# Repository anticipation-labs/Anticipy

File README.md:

# Anticipy

Anticipy is a proactive assistant. A phone, a pendant, or a Mac meeting
recorder captures speech; a per-owner server brain interprets it with context
and memory; approved work reaches the owner's own browser, connected apps, or
device "hands"; and every outcome comes back to the phone as a receipt.

**Work on `cloudflare-backend`.** It is the source of record. `main` is an
older, unrelated lineage and is never pushed to; pull requests target
`cloudflare-backend`. Read [HARNESS-LAWS.md](HARNESS-LAWS.md) before changing
anything: meaning belongs to a model with context, never to a regex, word
list, or threshold.

## Components

| Component | Path | What it is |
| --- | --- | --- |
| iPhone app | `app/ios/` | SwiftUI: listening and on-device transcription, pendant BLE (`app/ios/Anticipy/BLE/`), replies, connected apps |
| Mac app | `app/macos/` | Meeting recorder; unsigned build in CI, signed release through `mac-release.yml` |
| Chrome extension | `extension/` | MV3 "hands" in the owner's own logged-in Chrome; packaged into three ZIP aliases under `migration/workers/public/` |
| API Worker | `migration/workers/` | Cloudflare Worker (TypeScript) with D1, R2 and a Durable Object; the production API |
| D1 schema and migrations | `migration/d1/` | `schema.sql` plus dated additive migrations |
| Brain Worker + Python brain | `migration/workers/brain/`, `brain/` | Containers fleet, one container per owner, running the Python brain image |
| Pendant firmware | `firmware/` | Zephyr candidate for the XIAO nRF52840 Sense; host-checked here, not built or flashed |
| Gates and proofs | `overnight/`, `proof/` | Scoreboards and live or loopback proofs with green / red / UNPROVEN semantics |
| Python tests | `tests/` | pytest suite over the brain, the gates and a local D1 |
| Contracts | `migration/spec/CONTRACT.md`, `migration/workers/ARCHITECTURE.md` | Behavioural oracle and the Worker reference |

## Data flow

```text
pendant ─BLE─► iPhone ─┐
Mac recorder ──────────┼─► events (D1) ─► brain (one process per owner) ─► jobs ─► hands ─► receipt ─► iPhone
typed / text reply ────┘                   memory.db held in R2             browser · API · device
```

[docs/ARCHITECTURE.md](docs/ARCHITECTURE.md) explains each hop and the
contracts the runtimes share.

## Run every suite

```sh
PYTHON_DOTENV_DISABLED=1 python -m pytest -q
(cd migration/workers && npm test && npx tsc --noEmit)
npm test --prefix migration/workers/brain && npm run typecheck --prefix migration/workers/brain
node extension/tests/run_all.mjs
sh app/ios/Tests/run_all.sh
sh app/macos/Tests/run_all.sh
sh firmware/source/tests/run_firmware_tests.sh
python3 proof/audit/check_extension_package.py
```

[docs/TESTING.md](docs/TESTING.md) says what each suite proves, what it does
not, how to run them offline, and how the installed-extension proof rig works.

## Read next

- [Independent audit, September 15](research/2026-09-15-independent-app-audit.md):
  freshly reproduced checks, corrections to earlier claims, local build 178
  repairs and remaining live acceptance gaps.
- [September 13 readiness board](docs/EOD-READINESS-2026-09-13.md): the earlier
  release evidence and remaining-work board; read with the audit corrections.
- [CHANGELOG.md](CHANGELOG.md): what each release deployed, and what it did
  not prove.
- [docs/ARCHITECTURE.md](docs/ARCHITECTURE.md): runtimes, shared contracts,
  and the evidence ladder.
- [docs/RELEASE.md](docs/RELEASE.md): the ordered release runbook and
  rollback notes.
- [CONTRIBUTING.md](CONTRIBUTING.md): branch model, path-limited commits, the
  iOS build-number rule, and the review expectation.
- [SECURITY.md](SECURITY.md): how to report a vulnerability and where the
  private-data boundary sits.
- [HARNESS-LAWS.md](HARNESS-LAWS.md): the six laws that outrank everything
  else in this tree.
- [docs/README.md](docs/README.md): index of every document under `docs/`.

## License

MIT; see [LICENSE](LICENSE). Third-party code vendored in this tree is listed
in [THIRD_PARTY_NOTICES.md](THIRD_PARTY_NOTICES.md).

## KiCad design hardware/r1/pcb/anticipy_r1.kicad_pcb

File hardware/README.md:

# Anticipy Hardware V1 — end-to-end build package

Goal: Anticipy-branded always-on pendant. Streams audio to iPhone over BLE,
records offline to flash when the phone is away (20 h backlog), back-syncs on
reconnect, 16 h+ speaking-time battery, VAD, side button, haptic feedback.
First units hand-assembled (week 1), customer wave (week 2).

## Contents

| Path | What |
|---|---|
| `case_v7/` | Pendant case v7 "Plaud envelope" — parametric SCAD, print-ready STLs, render |
| `case_v7/BUILD_GUIDE.md` | Print settings, wiring, soldering order, assembly |
| `firmware/README.md` | Omi-fork firmware plan: build target, haptic patch, flash procedure |
| `ORDERING.md` | Exact carts (RobotShop, Amazon.ca, JLC3DP, Apple) with prices |
| `EXECUTION_PLAN.md` | Day-by-day 2-week schedule, costs, risks, compliance |
| `qa/QA_CHECKLIST.md` | Per-unit acceptance test before a unit ships |

## Size target vs. reality (stated straight)

Reference: Plaud NotePin 51 × 21 × 11 mm; +15% margin = **58.7 × 24.2 × 12.65 mm**.

v7 measures **67.9 × 26.3 × 12.8 mm** (STL-verified). Thickness hits the
envelope; width is 2 mm over; length is 9 mm over because an off-the-shelf
XIAO nRF52840 Sense (21 mm) must sit beside a 30.5 mm 250 mAh cell — physics,
not laziness. The true Plaud envelope requires the custom-PCB phase
(nRF52840-QIAA directly on the board, cell over the board), which is the
week-3+ V2 board. v7 is still Plaud-NotePin *class*: pill-shaped, domed,
chain-hung, under 13 mm thin.

## Architecture (decided)

- **MCU/radio/mic**: Seeed XIAO nRF52840 Sense (FCC modular approval
  Z4T-XIAONRF52840 — the only legal fast path to customer radios in 2 weeks).
  Onboard PDM mic, BLE 5, BQ25101 LiPo charger, USB-C.
- **Battery**: 502030 250 mAh LiPo → ~11–16 h streaming (est., must be
  measured on unit #1), ~30 h offline. Not validated yet — QA step 8.
- **Offline backlog**: W25Q128 16 MB SPI flash breakout (ADPCM 4 KB/s ≈ 70 min
  continuous; with VAD gating ≈ 6–8 h of real speech). For a guaranteed
  20 h continuous: substitute the microSD SPI module (same 4 SPI pins) —
  case has room; both wirings in the build guide.
- **Firmware**: fork of Omi (MIT) Zephyr firmware — BLE audio service,
  offline storage + back-sync, button events already implemented. We add
  haptics + Anticipy device name. See `firmware/README.md`.
- **App**: Omi's open-source Flutter app rebranded Anticipy on TestFlight
  (week 1: stock protocol-compatible app for bring-up).
- **Haptics**: 10 mm coin motor, NPN low-side driver on a GPIO.
- **Shells**: FDM (Bambu P2S, silver PETG Pro) for week-1 units; JLC3DP
  SLM titanium prints of the same STLs for the customer wave.

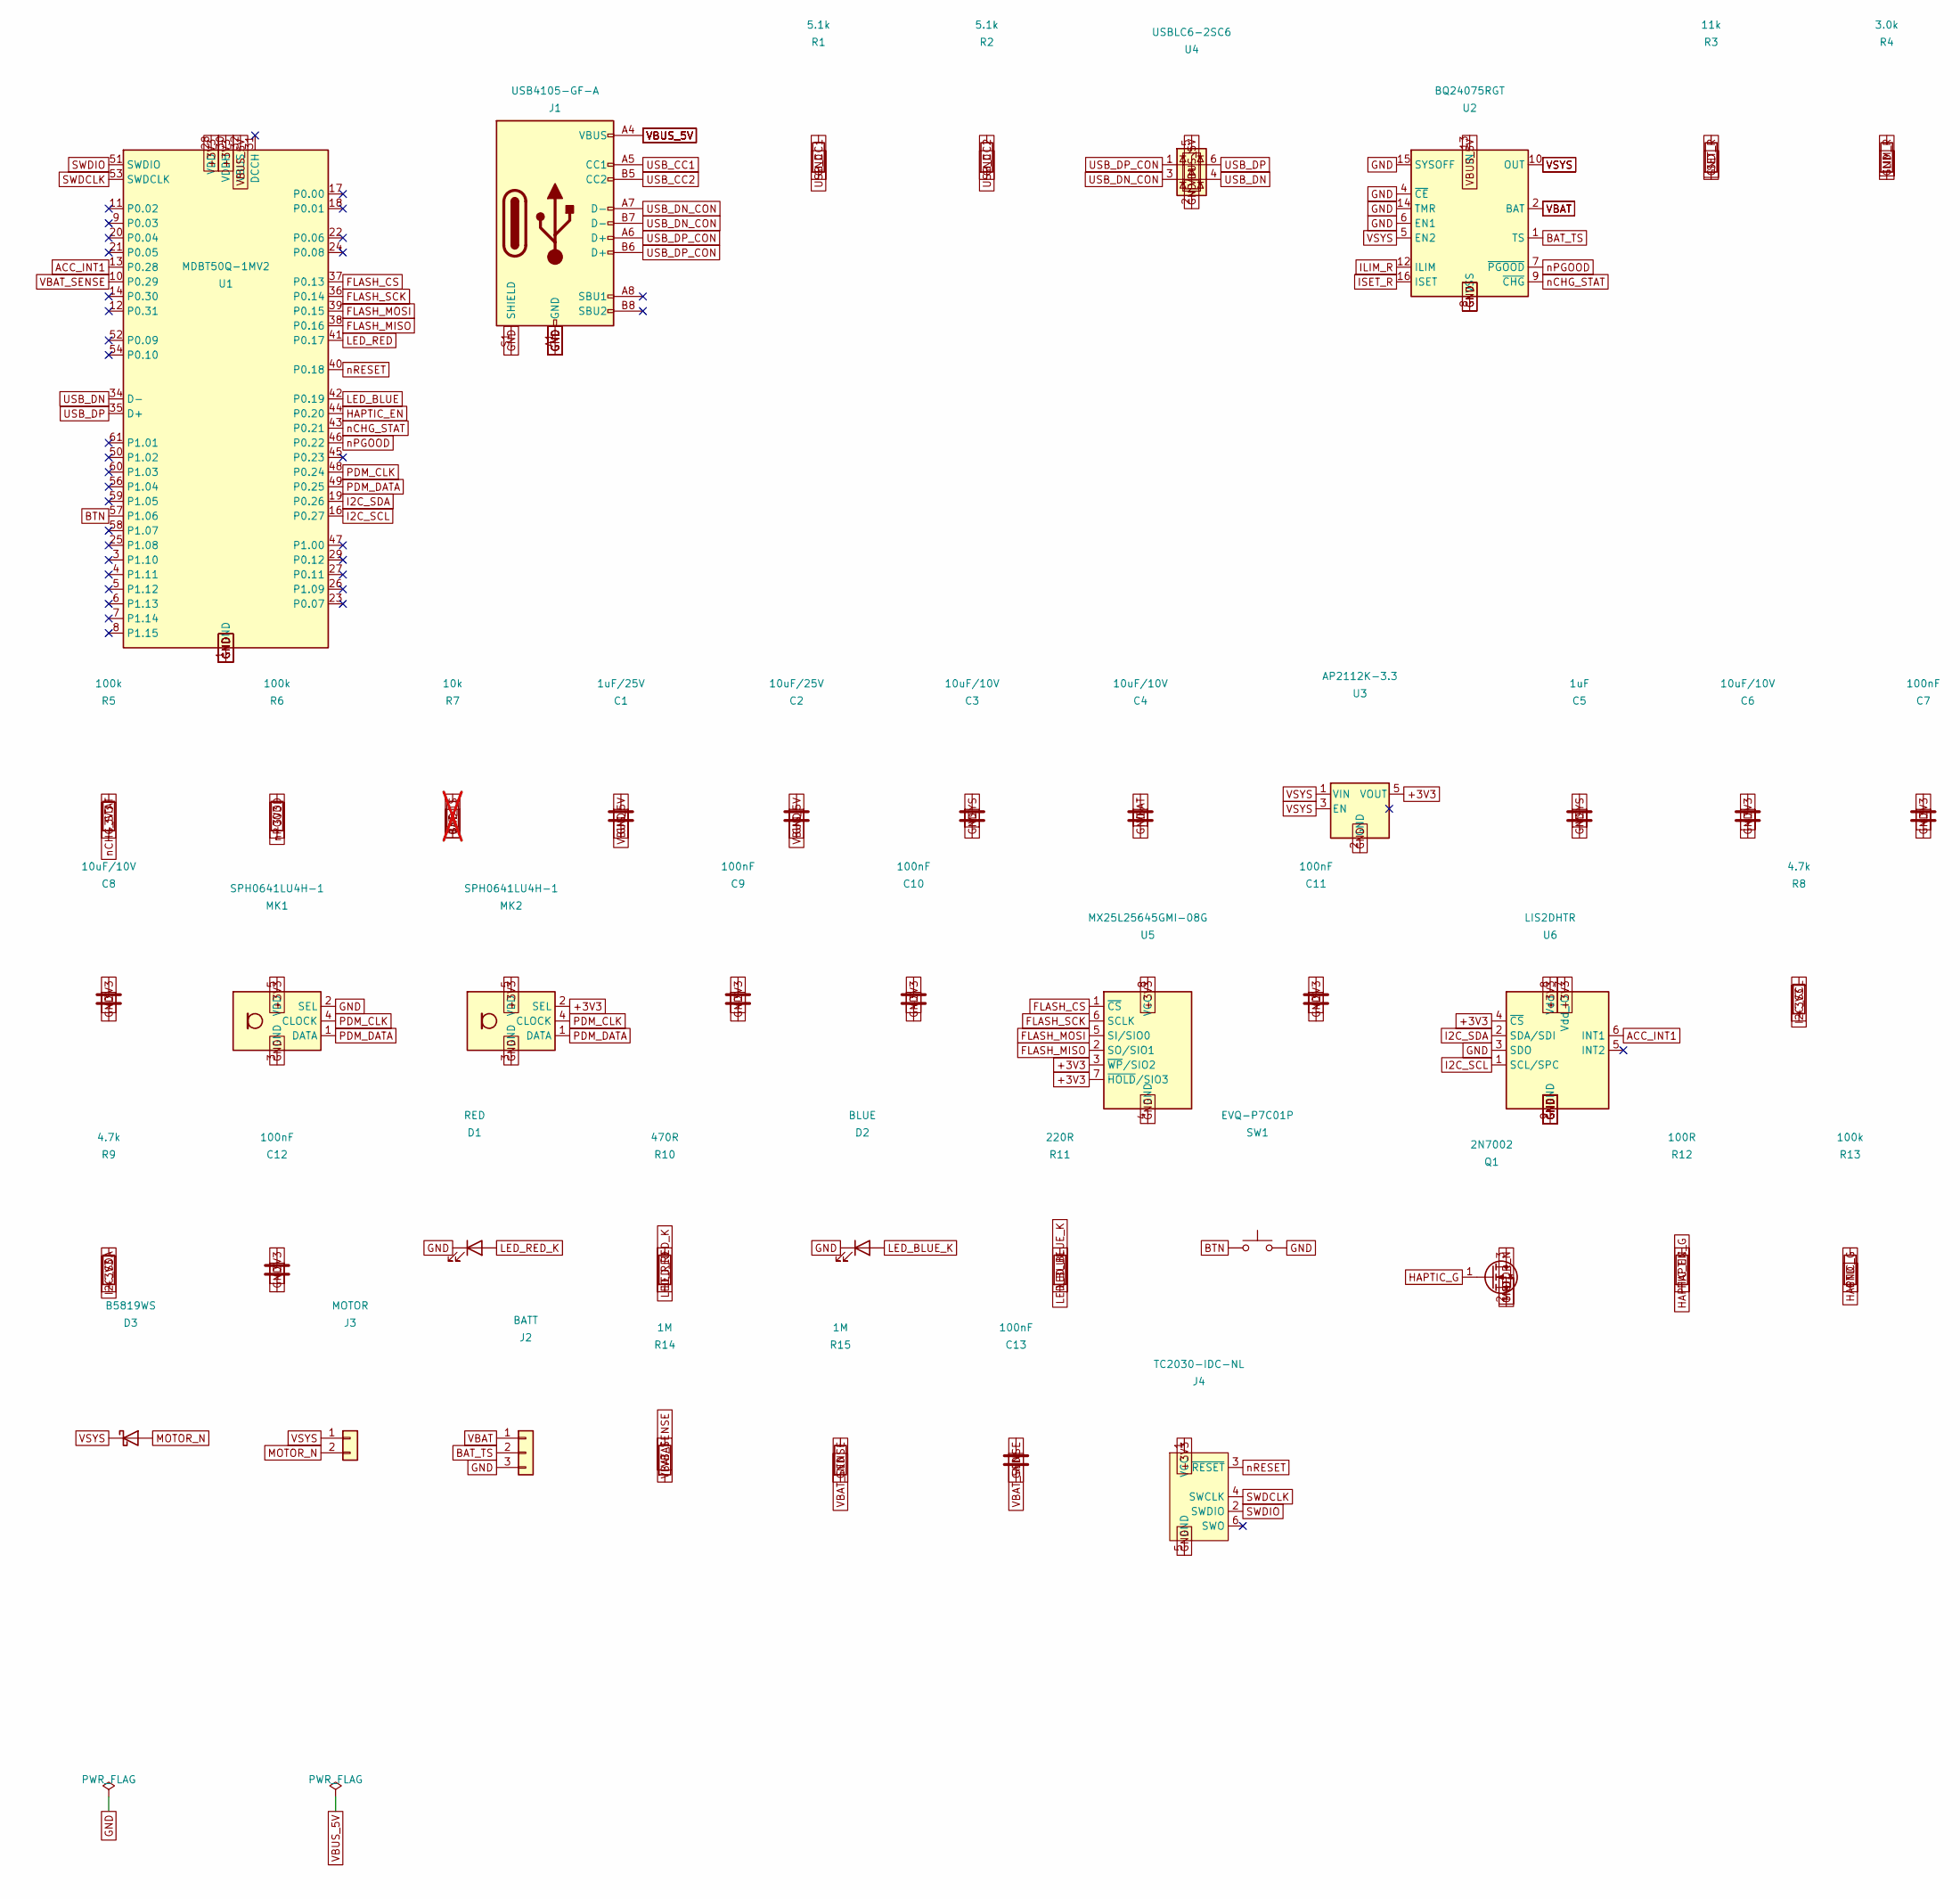
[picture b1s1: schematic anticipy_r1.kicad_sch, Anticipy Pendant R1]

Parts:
C1: 1uF/25V; C_0603_1608Metric; MPN Murata GRM188R61E105KA12
C2: 10uF/25V; C_0805_2012Metric; MPN Murata GRM21BR61E106KA73
C3, C4, C6, C8: 10uF/10V; C_0805_2012Metric; MPN Murata GRM21BR61A106KE19
C5: 1uF; C_0603_1608Metric; MPN Murata GRM188R61A105KA61
C7, C9, C10, C11, C12, C13: 100nF; C_0402_1005Metric; MPN Murata GRM155R71C104KA88
D1: RED; LED_0603_1608Metric; MPN Lite-On LTST-C193KRKT-5A
D2: BLUE; LED_0603_1608Metric; MPN Lite-On LTST-C193TBKT-5A
D3: B5819WS; D_SOD-323; MPN Vishay B5819WS-TP
J1: USB4105-GF-A; USB_C_Receptacle_GCT_USB4105-xx-A_16P_TopMnt_Horizontal; MPN GCT USB4105-GF-A
J2: BATT; JST_SH_SM03B-SRSS-TB_1x03-1MP_P1.00mm_Horizontal; MPN JST SM03B-SRSS-TB
J3: MOTOR; JST_SH_SM02B-SRSS-TB_1x02-1MP_P1.00mm_Horizontal; MPN JST SM02B-SRSS-TB
J4: TC2030-IDC-NL; Tag-Connect_TC2030-IDC-NL_2x03_P1.27mm_Vertical; MPN Tag-Connect TC2030-IDC-NL
MK1, MK2: SPH0641LU4H-1; Knowles_LGA-5_3.5x2.65mm; MPN Knowles SPH0641LU4H-1
Q1: 2N7002; SOT-23; MPN onsemi 2N7002LT1G
R1, R2: 5.1k; R_0402_1005Metric; MPN Yageo RC0402FR-075K1L
R3: 11k; R_0402_1005Metric; MPN Yageo RC0402FR-0711KL
R4: 3.0k; R_0402_1005Metric; MPN Yageo RC0402FR-073KL
R5, R6, R13: 100k; R_0402_1005Metric; MPN Yageo RC0402FR-07100KL
R7: 10k; R_0402_1005Metric; MPN Yageo RC0402FR-0710KL; not fitted
R8, R9: 4.7k; R_0402_1005Metric; MPN Yageo RC0402FR-074K7L
R10: 470R; R_0402_1005Metric; MPN Yageo RC0402FR-07470RL
R11: 220R; R_0402_1005Metric; MPN Yageo RC0402FR-07220RL
R12: 100R; R_0402_1005Metric; MPN Yageo RC0402FR-07100RL
R14, R15: 1M; R_0402_1005Metric; MPN Yageo RC0402FR-071ML
SW1: EVQ-P7C01P; SW_SPST_EVQP7C; MPN Panasonic EVQ-P7C01P
U1: MDBT50Q-1MV2; Raytac_MDBT50Q; MPN Raytac MDBT50Q-1MV2
U2: BQ24075RGT; VQFN-16-1EP_3x3mm_P0.5mm_EP1.6x1.6mm; MPN TI BQ24075RGTR
U3: AP2112K-3.3; SOT-23-5; MPN Diodes AP2112K-3.3TRG1
U4: USBLC6-2SC6; SOT-23-6; MPN ST USBLC6-2SC6
U5: MX25L25645GMI-08G; SOIC-8_5.3x5.3mm_P1.27mm; MPN Macronix MX25L25645GMI-08G
U6: LIS2DHTR; LGA-14_2x2mm_P0.35mm_LayoutBorder3x4y; MPN ST LIS2DHTR

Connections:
+3V3: C6.1, C7.1, C8.1, C9.1, C10.1, C11.1, C12.1, J4.1 (VCC), MK1.5 (VDD), MK2.2 (SEL), MK2.5 (VDD), R5.2, R6.2, R8.2, R9.2, U1.28 (VDD), U1.30 (VDDH), U3.5 (VOUT), U5.3 (~WP/SIO2), U5.7 (~HOLD/SIO3), U5.8 (VCC), U6.4 (~CS), U6.7 (Vdd_IO), U6.8 (Vdd)
ACC_INT1: U1.13 (P0.28), U6.6 (INT1)
BAT_TS: J2.2, R7.1, U2.1 (TS)
BTN: SW1.1, U1.57 (P1.06)
FLASH_CS: U1.37 (P0.13), U5.1 (~CS)
FLASH_MISO: U1.38 (P0.16), U5.2 (SO/SIO1)
FLASH_MOSI: U1.39 (P0.15), U5.5 (SI/SIO0)
FLASH_SCK: U1.36 (P0.14), U5.6 (SCLK)
GND: C1.2, C2.2, C3.2, C4.2, C5.2, C6.2, C7.2, C8.2, C9.2, C10.2, C11.2, C12.2, C13.2, D1.1 (K), D2.1 (K), J1.A1 (GND), J1.A12 (GND), J1.B1 (GND), J1.B12 (GND), J1.S1 (SHIELD), J2.3, J4.5 (GND), MK1.2 (SEL), MK1.3 (GND), MK2.3 (GND), Q1.2 (S), R1.2, R2.2, R3.2, R4.2, R7.2, R13.2, R15.2, SW1.2, U1.1 (GND), U1.2 (GND), U1.15 (GND), U1.33 (GND), U1.55 (GND), U2.4 (~CE), U2.6 (EN1), U2.8 (VSS), U2.14 (TMR), U2.15 (SYSOFF), U2.17 (VSS), U3.2 (GND), U4.2 (GND), U5.4 (GND), U6.3 (SDO), U6.9 (GND), U6.10 (GND), U6.11 (GND), U6.12 (GND), U6.13 (GND), U6.14 (GND)
HAPTIC_EN: R12.1, U1.44 (P0.20)
HAPTIC_G: Q1.1 (G), R12.2, R13.1
I2C_SCL: R8.1, U1.16 (P0.27), U6.1 (SCL/SPC)
I2C_SDA: R9.1, U1.19 (P0.26), U6.2 (SDA/SDI)
ILIM_R: R4.1, U2.12 (ILIM)
ISET_R: R3.1, U2.16 (ISET)
LED_BLUE: R11.1, U1.42 (P0.19)
LED_BLUE_K: D2.2 (A), R11.2
LED_RED: R10.1, U1.41 (P0.17)
LED_RED_K: D1.2 (A), R10.2
MOTOR_N: D3.2 (A), J3.2, Q1.3 (D)
PDM_CLK: MK1.4 (CLOCK), MK2.4 (CLOCK), U1.48 (P0.24)
PDM_DATA: MK1.1 (DATA), MK2.1 (DATA), U1.49 (P0.25)
SWDCLK: J4.4 (SWCLK), U1.53 (SWDCLK)
SWDIO: J4.2 (SWDIO), U1.51 (SWDIO)
USB_CC1: J1.A5 (CC1), R1.1
USB_CC2: J1.B5 (CC2), R2.1
USB_DN: U1.34 (D-), U4.4 (I/O2)
USB_DN_CON: J1.A7 (D-), J1.B7 (D-), U4.3 (I/O2)
USB_DP: U1.35 (D+), U4.6 (I/O1)
USB_DP_CON: J1.A6 (D+), J1.B6 (D+), U4.1 (I/O1)
VBAT: C4.1, J2.1, R14.1, U2.2 (BAT), U2.3 (BAT)
VBAT_SENSE: C13.1, R14.2, R15.1, U1.10 (P0.29)
VBUS_5V: C1.1, C2.1, J1.A4 (VBUS), J1.A9 (VBUS), J1.B4 (VBUS), J1.B9 (VBUS), U1.32 (VBUS), U2.13 (IN), U4.5 (VBUS)
VSYS: C3.1, C5.1, D3.1 (K), J3.1, U2.5 (EN2), U2.10 (OUT), U2.11 (OUT), U3.1 (VIN), U3.3 (EN)
nCHG_STAT: R5.1, U1.43 (P0.21), U2.9 (~CHG)
nPGOOD: R6.1, U1.46 (P0.22), U2.7 (~PGOOD)
nRESET: J4.3 (~RESET), U1.40 (P0.18)

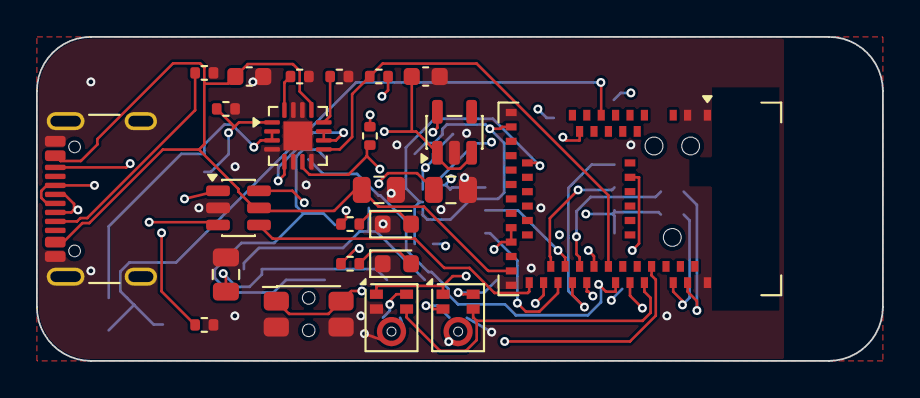
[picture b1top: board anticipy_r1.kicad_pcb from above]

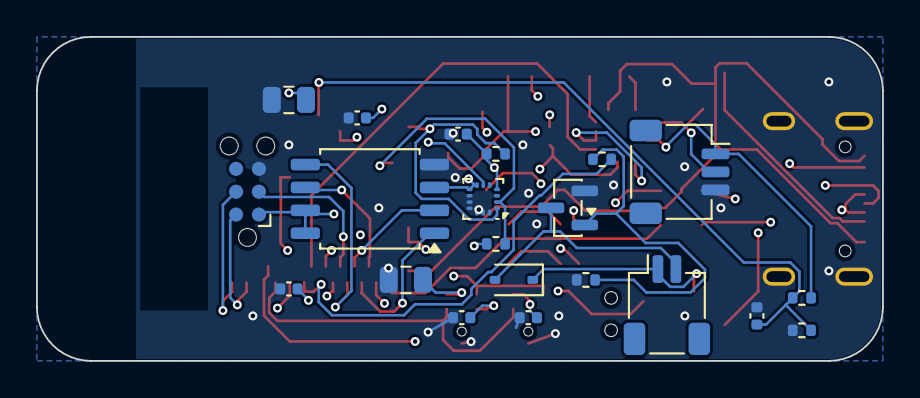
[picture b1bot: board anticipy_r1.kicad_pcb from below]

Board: 4 copper layers, 47.0 x 18.0 mm, 45 parts (21 on the bottom side), 37 nets.

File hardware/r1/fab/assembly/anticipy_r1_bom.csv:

Designators,Qty,Value,Footprint,Manufacturer Part Number
C1,1,1uF/25V,Capacitor_SMD:C_0603_1608Metric,Murata GRM188R61E105KA12
C2,1,10uF/25V,Capacitor_SMD:C_0805_2012Metric,Murata GRM21BR61E106KA73
"C3,C4,C6,C8",4,10uF/10V,Capacitor_SMD:C_0805_2012Metric,Murata GRM21BR61A106KE19
C5,1,1uF,Capacitor_SMD:C_0603_1608Metric,Murata GRM188R61A105KA61
"C10,C11,C12,C13,C7,C9",6,100nF,Capacitor_SMD:C_0402_1005Metric,Murata GRM155R71C104KA88
D1,1,RED,LED_SMD:LED_0603_1608Metric,Lite-On LTST-C193KRKT-5A
D2,1,BLUE,LED_SMD:LED_0603_1608Metric,Lite-On LTST-C193TBKT-5A
D3,1,B5819WS,Diode_SMD:D_SOD-323,Vishay B5819WS-TP
J1,1,USB4105-GF-A,Connector_USB:USB_C_Receptacle_GCT_USB4105-xx-A_16P_TopMnt_Horizontal,GCT USB4105-GF-A
J2,1,BATT,Connector_JST:JST_SH_SM03B-SRSS-TB_1x03-1MP_P1.00mm_Horizontal,JST SM03B-SRSS-TB
J3,1,MOTOR,Connector_JST:JST_SH_SM02B-SRSS-TB_1x02-1MP_P1.00mm_Horizontal,JST SM02B-SRSS-TB
J4,1,TC2030-IDC-NL,Connector:Tag-Connect_TC2030-IDC-NL_2x03_P1.27mm_Vertical,Tag-Connect TC2030-IDC-NL
"MK1,MK2",2,SPH0641LU4H-1,Sensor_Audio:Knowles_LGA-5_3.5x2.65mm,Knowles SPH0641LU4H-1
Q1,1,2N7002,Package_TO_SOT_SMD:SOT-23,onsemi 2N7002LT1G
"R1,R2",2,5.1k,Resistor_SMD:R_0402_1005Metric,Yageo RC0402FR-075K1L
R10,1,470R,Resistor_SMD:R_0402_1005Metric,Yageo RC0402FR-07470RL
R11,1,220R,Resistor_SMD:R_0402_1005Metric,Yageo RC0402FR-07220RL
R12,1,100R,Resistor_SMD:R_0402_1005Metric,Yageo RC0402FR-07100RL
"R14,R15",2,1M,Resistor_SMD:R_0402_1005Metric,Yageo RC0402FR-071ML
R3,1,11k,Resistor_SMD:R_0402_1005Metric,Yageo RC0402FR-0711KL
R4,1,3.0k,Resistor_SMD:R_0402_1005Metric,Yageo RC0402FR-073KL
"R13,R5,R6",3,100k,Resistor_SMD:R_0402_1005Metric,Yageo RC0402FR-07100KL
R7,1,10k,Resistor_SMD:R_0402_1005Metric,Yageo RC0402FR-0710KL
"R8,R9",2,4.7k,Resistor_SMD:R_0402_1005Metric,Yageo RC0402FR-074K7L
SW1,1,EVQ-P7C01P,Button_Switch_SMD:SW_SPST_EVQP7C,Panasonic EVQ-P7C01P
U1,1,MDBT50Q-1MV2,RF_Module:Raytac_MDBT50Q,Raytac MDBT50Q-1MV2
U2,1,BQ24075RGT,Package_DFN_QFN:VQFN-16-1EP_3x3mm_P0.5mm_EP1.6x1.6mm,TI BQ24075RGTR
U3,1,AP2112K-3.3,Package_TO_SOT_SMD:SOT-23-5,Diodes AP2112K-3.3TRG1
U4,1,USBLC6-2SC6,Package_TO_SOT_SMD:SOT-23-6,ST USBLC6-2SC6
U5,1,MX25L25645GMI-08G,Package_SO:SOIC-8_5.3x5.3mm_P1.27mm,Macronix MX25L25645GMI-08G
U6,1,LIS2DHTR,Package_LGA:LGA-14_2x2mm_P0.35mm_LayoutBorder3x4y,ST LIS2DHTR

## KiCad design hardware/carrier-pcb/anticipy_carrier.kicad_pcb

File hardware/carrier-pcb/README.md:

# Anticipy V1 carrier PCB

53.0 × 19.5 mm, 2-layer board that turns each unit from ~45 min of hand-wiring
into ~10 min of soldering: drop the XIAO nRF52840 Sense onto the 14 header
pads, everything else is already on the board.

## What's on it
| Ref | Part | Job |
|---|---|---|
| U1 | XIAO nRF52840 Sense (module, 2×7 pins 2.54 mm) | brain / BLE / mic / charger |
| U2 | W25Q128JVSIQ (SOIC-8) | 16 MB offline backlog flash |
| Q1 | S8050 (SOT-23) | haptic motor low-side driver |
| R1 | 1 kΩ 0805 | base resistor |
| D1 | 1N4148W (SOD-123) | motor flyback diode |
| C1 | 100 nF 0805 | flash decoupling |
| J1 | 4 wire pads | BTN1/BTN2 (side button), MOT+/MOT− (coin motor) |

Battery: solder the 502030 cell leads directly to the XIAO underside BAT+/BAT−
pads (charging stays on the XIAO's built-in charger). The cell tapes over the
bare right half of this board.

## Nets
GND zone on F.Cu, 3V3 zone on B.Cu. Signals: D1=BTN, D2=CS, D3=HAP_CTRL,
D8=SCK, D9=MISO, D10=MOSI — matches `../case_v7/BUILD_GUIDE.md`.

## Files
- `generate_carrier.py` — regenerates everything (KiCad 6 pcbnew scripting)
- `anticipy_carrier.kicad_pcb` — the board (open in KiCad)
- `drc_report.txt` — **0 violations, 0 unconnected pads** (KiCad 6 DRC)
- `gerbers/` — fab-ready Gerbers + Excellon drill files (zip this folder and
  upload to jlcpcb.com; 2-layer, 1.6 mm, HASL, any color)
- `render/` — copper renders (front / back)

## Status — honest
- DRC-clean and fully routed: YES (electrically verified in software).
- Physically fabbed and tested: NO — order 5 from JLCPCB (~$4 + ship,
  24–48 h fab) and bring one up before committing the batch to it.
- Week-1 unit does NOT need this board (6 hand-soldered wires per the build
  guide); it's for the 12-unit customer batch.
- W25Q128 = 16 MB ≈ 6–8 h of VAD-gated speech. If a guaranteed 20 h
  continuous backlog is required, swap U2 for a microSD socket rev (same SPI
  nets, footprint change only).

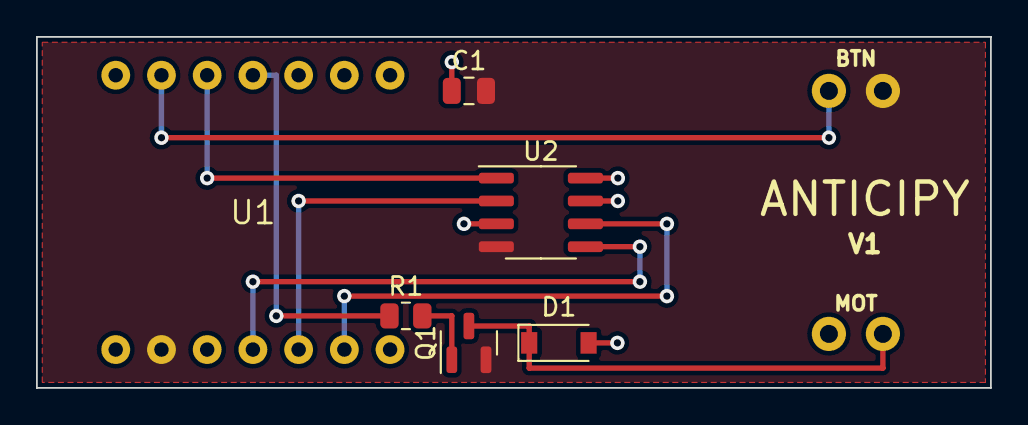
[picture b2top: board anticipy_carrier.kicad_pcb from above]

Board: 2 copper layers, 53.0 x 19.5 mm, 7 parts (0 on the bottom side), 10 nets.

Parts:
C1: 100n; C_0805_2012Metric
D1: 1N4148W; D_SOD-123
J1: wires
Q1: S8050; SOT-23
R1: 1k; R_0805_2012Metric
U1: XIAO nRF52840 Sense
U2: W25Q128JVSIQ; SOIC-8_3.9x4.9mm_P1.27mm

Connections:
3V3: C1.1, D1.2, J1.MOT+, U1.3V3, U2.3, U2.7, U2.8
BTN: J1.BTN1, U1.D1
CS: U1.D2, U2.1
GND: C1.2, J1.BTN2, Q1.2, U1.GND, U2.4
HAP_CTRL: R1.1, U1.D3
MISO: U1.D9, U2.2
MOSI: U1.D10, U2.5
MOT_SW: D1.1, J1.MOT-, Q1.3
NPN_B: Q1.1, R1.2
SCK: U1.D8, U2.6
